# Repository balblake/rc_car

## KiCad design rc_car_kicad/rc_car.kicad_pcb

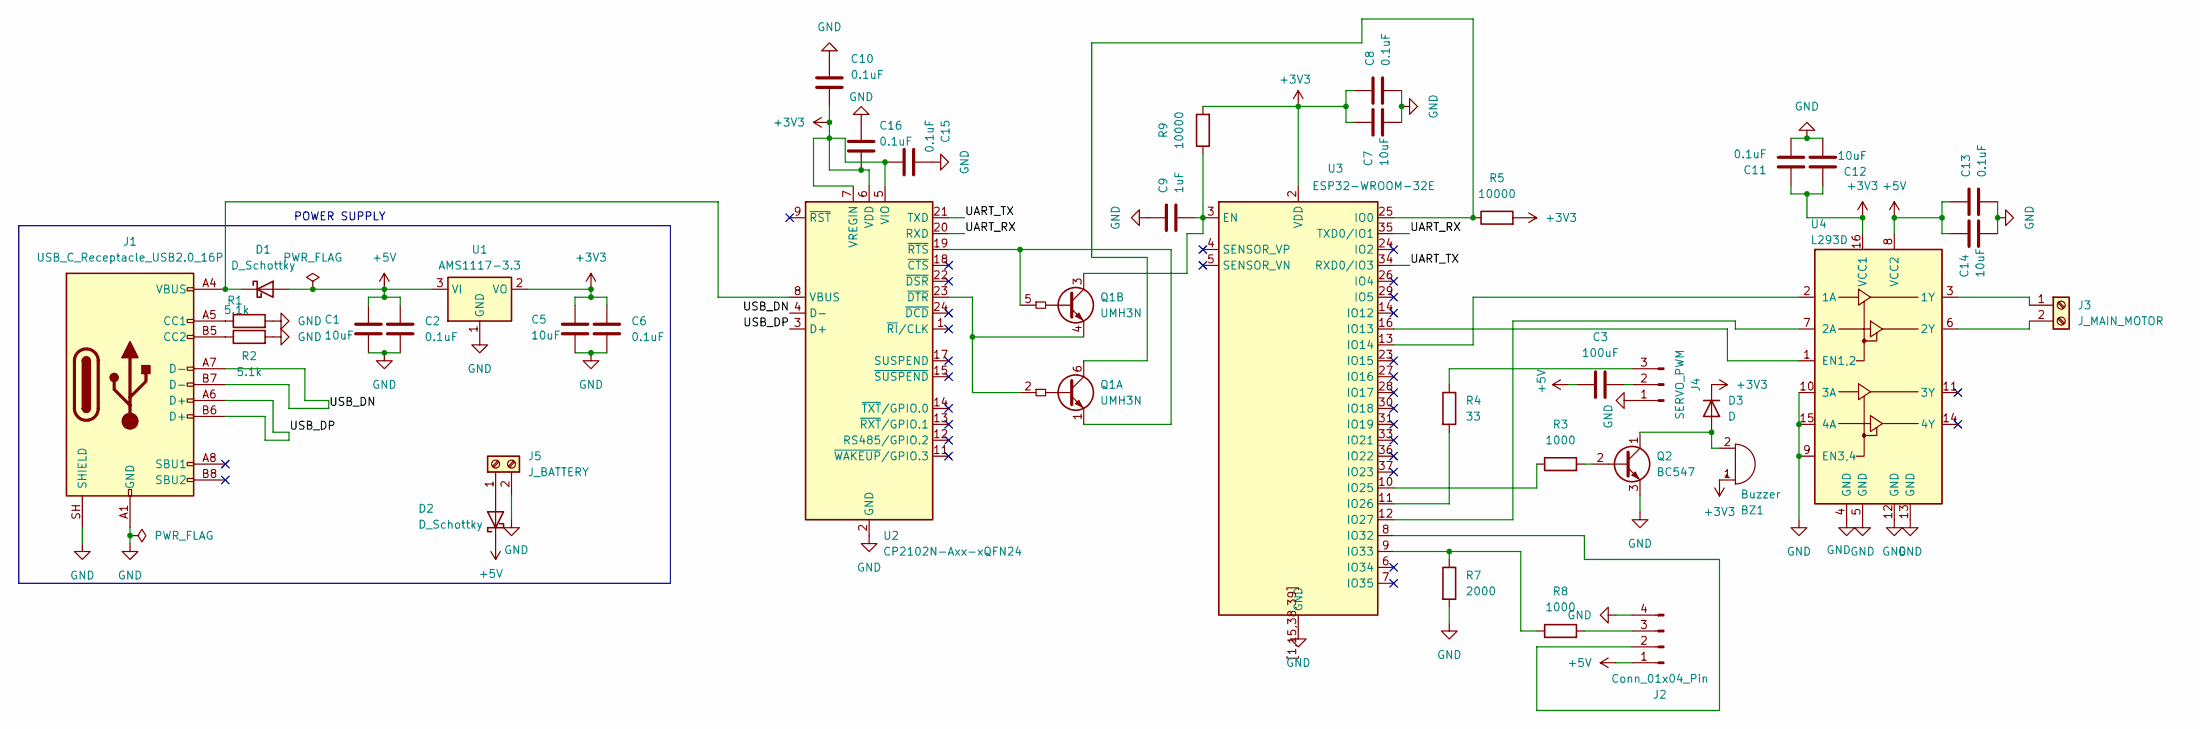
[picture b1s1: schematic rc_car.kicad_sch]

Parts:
BZ1: Buzzer; Buzzer_12x9.5RM7.6
C1, C5, C7, C12, C14: 10uF; C_0805_2012Metric
C2, C6, C8, C10, C11, C13, C15, C16: 0.1uF; C_0805_2012Metric
C3: 100uF; C_0805_2012Metric
C9: 1uF; C_0805_2012Metric
D1, D2: D_Schottky; D_SOD-123
D3: D; D_DO-35_SOD27_P7.62mm_Horizontal
J1: USB_C_Receptacle_USB2.0_16P; USB_C_Receptacle_HRO_TYPE-C-31-M-12
J2: Conn_01x04_Pin; PinHeader_1x04_P2.54mm_Vertical
J3: J_MAIN_MOTOR; TerminalBlock_Phoenix_PT-1,5-2-5.0-H_1x02_P5.00mm_Horizontal
J4: SERVO_PWM; PinHeader_1x03_P2.54mm_Vertical
J5: J_BATTERY; TerminalBlock_Phoenix_PT-1,5-2-5.0-H_1x02_P5.00mm_Horizontal
Q1: UMH3N; SOT-363_SC-70-6
Q2: BC547; TO-92_Inline
R1, R2: 5.1k; R_0805_2012Metric
R3, R8: 1000; R_0805_2012Metric
R4: 33; R_0805_2012Metric
R5, R9: 10000; R_0805_2012Metric
R7: 2000; R_0805_2012Metric
U1: AMS1117-3.3; SOT-223-3_TabPin2
U2: CP2102N-Axx-xQFN24; QFN-24-1EP_4x4mm_P0.5mm_EP2.6x2.6mm
U3: ESP32-WROOM-32E
U4: L293D; DIP-16_W7.62mm

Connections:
+3V3: BZ1.1 (+), C5.1, C6.1, C7.1, C8.1, C10.2, C11.1, C12.1, C15.2, C16.2, D3.1 (K), R5.2, R9.2, U1.2 (VO), U2.5 (VIO), U2.6 (VDD), U2.7 (VREGIN), U3.2 (VDD), U4.16 (VCC1)
+5V: C1.1, C2.1, C3.1, C13.1, C14.1, D1.2 (A), D2.1 (K), J2.1, U1.3 (VI), U4.8 (VCC2)
/UART_RX: U2.20 (RXD), U3.35 (TXD0/IO1)
/UART_TX: U2.21 (TXD), U3.34 (RXD0/IO3)
/USB_DN: J1.A7 (D-), J1.B7 (D-), U2.4 (D-)
/USB_DP: J1.A6 (D+), J1.B6 (D+), U2.3 (D+)
GND: C1.2, C2.2, C5.2, C6.2, C7.2, C8.2, C9.1, C10.1, C11.2, C12.2, C13.2, C14.2, C15.1, C16.1, J1.A1 (GND), J1.A12 (GND), J1.B1 (GND), J1.B12 (GND), J1.SH (SHIELD), J2.4, J4.1, J5.2, Q2.3 (E), R1.2, R2.2, R7.2, U1.1 (GND), U2.2 (GND), U2.25 (GND), U3.1 (GND), U3.15 (GND), U3.38 (GND), U3.39 (GND), U3.[1,15,38,39] (GND), U4.4 (GND), U4.5 (GND), U4.9 (EN3,4), U4.10 (3A), U4.12 (GND), U4.13 (GND), U4.15 (4A)
unnamed: BZ1.2 (-), D3.2 (A), Q2.1 (C)
unnamed: D1.1 (K), J1.A4 (VBUS), J1.A9 (VBUS), J1.B4 (VBUS), J1.B9 (VBUS), U2.8 (VBUS)
unnamed: D2.2 (A), J5.1
unnamed: J1.A5 (CC1), R1.1
unnamed: J1.B5 (CC2), R2.1
unnamed: J2.2, U3.8 (IO32)
unnamed: J2.3, R8.2
unnamed: J3.1, U4.3 (1Y)
unnamed: J3.2, U4.6 (2Y)
unnamed: C3.2, J4.2
unnamed: J4.3, R4.1
unnamed: Q1.2 (B1), Q1.4 (E2), U2.23 (~DTR)
unnamed: Q1.6 (C1), R5.1, U3.25 (IO0)
unnamed: Q1.1 (E1), Q1.5 (B2), U2.19 (~RTS)
unnamed: C9.2, Q1.3 (C2), R9.1, U3.3 (EN)
unnamed: Q2.2 (B), R3.2
unnamed: U3.16 (IO13), U4.1 (EN1,2)
unnamed: U3.13 (IO14), U4.2 (1A)
unnamed: R3.1, U3.10 (IO25)
unnamed: R4.2, U3.11 (IO26)
unnamed: U3.12 (IO27), U4.7 (2A)
unnamed: R7.1, R8.1, U3.9 (IO33)

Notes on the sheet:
POWER SUPPLY

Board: 2 copper layers, 38 parts (0 on the bottom side), 29 nets, no tracks yet.

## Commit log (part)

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2026-06-14 initial
2026-06-14 remove kicad files from main
2026-06-14 main.cpp
2026-06-14 added kicad as a submodule
